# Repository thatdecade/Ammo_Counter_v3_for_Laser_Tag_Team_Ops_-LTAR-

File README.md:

# Ammo Counter for Laser Tag Team Ops (ZZLT)
This is my third attempt at making an Ammo Counter for the LTAR tagger.  This version connects to the LTAR's headphone jack to receive game data.  It was designed in collaboration with Ryan Bales.

The advantages of the ZZLT LTAR Display over my v2 LTAR Number Display are numerous.
- Bar graph indicator to match previous generation LTX displays
- Leverages the LTAR headphone jack to be compatible with all game modes!!!
- Lower power requirements
- Designed to match contours of LTAR iron sight
- Advanced modes to find player number in hosted games
- Easier installation, just 4 wires.

PCB Order Page:             
https://www.oshpark.com/shared_projects/LcxApEpA

Photo Gallery:          
https://www.flickr.com/photos/dwest2/albums/72157642762403194

Install Video:           
https://www.youtube.com/watch?v=OvuctqtzjE8

**Usage:**

The display will turn itself on and off. When you turn the tagger on, the display detects that and turns on. When the display first turns on, it will blink a single LED, just to let you know it's working. When you turn the tagger off, the display will stay on for about 15 seconds, and then turn off.

While you set up the LTAR, be it joining a game, or changing the health/team settings for a grab-and-go game, that single LED will continue to blink.

When the tagger starts it's countdown, the display will start showing how much time is left in the countdown! If you've used an LTX, the way it's shown should be very familiar to you. A blinking LED counts as 1, and a solid LED is 2.

Once the game starts, the countdown display will disappear and one of the mode LEDs at the bottom will light up. This is "Health" mode. It shows how much health you have left. This is displayed as a rough percentage of how much health you started the game with. A blinking LED is 6.25%, and a solid LED is 12.5%. While it may not be an exact display, it will give you an idea of when you need to start worrying.

If you press the button, the mode LED will change, and you'll be in Ammo mode. This shows you how much ammo is left in your clip. This is, once again, a percentage of how much ammo you started with. It will adapt automatically to any weapon, including but not limited to the pistol and machinegun built into the tagger.

One more press of the button, and you're in Shields mode! This one's a bit different. The tagger's shield can only be used in 10-second bursts, so the display shows a percentage based on whether you have 10 seconds worth of shield remaining. While your shield is on, this will show you how much time you have left in this burst of shields. When you turn off your shields, it will show you how much time is left until the cooldown of the shields finishes. The cooldown is shown as a "climbing" percentage, starting at 0% and going up to 100%. Once the cooldown finishes, it goes back to the display of whether you have 10 seconds remaining or not.

There is also a context-sensitive display, that will only be shown in certain types of hosted games. While not all of the features of this mode can be active at the same time, nothing in this mode overlaps between game modes.
- If you're neutralized, the center two LEDs in the vertical bar will be blinking.
- If you're in a zone game, you're neutralized, and the zone is hostile currently, the top and bottom LED of the vertical LED bar will be blinking.
- Some taggers might be able to show when you gain a zone point, in which case the 2nd, 3rd, 6th and 7th LEDs of the vertical LED bar will be lit up.
- If you're in a hunter/hunted game, when the hunting/hunted teams switch, the mode LEDs will show you which team you should be hunting by blinking the mode LED related to that team, and the team you should be avoiding is solid. The Health LED is Team 1, the Ammo LED is Team 2, and the Shield LED is Team 3.

When a game ends, whether by you being tagged out, or the time running out, it will go to a "game over" mode that has a few submodes. All of these modes display information in roughly the same way. Like other numerical modes, a blinking LED is "1", and a solid LED is "2". The top three LEDs of the vertical LED bar show the tens place, and the bottom five show the ones place.
- By default, the "game over" mode shows your player ID. The tens place represents the team, and the ones place represents your player number on that team.
- Some taggers might be able to show your team and player rank, if in a hosted game. If available, you will be able to press the button and cycle through them. After the player ID, first comes your team rank, followed by your personal rank.

This covers the basic operation of the LTAR display! There are a few extra modes, however.
- If you hold the button for a few seconds, all the LEDs will turn on, and the mode will reset to the Health mode. You're now in advanced mode! You can switch back to basic mode the same way.

If you cycle through the modes again, you'll find a few extras, which light up multiple mode LEDs.
- The first Advanced mode, with the Health and Ammo LEDs lit up, is "Game time" mode. In a non-hosted game, this will count up, and show how long you've been playing! This is limited to 69 minutes, however. Past that, it won't show the tens place. In a hosted game, this will count /down/, and tell how many minutes are left in the game.
- The second Advanced mode, with the Ammo and Shield LEDs lit up, shows you who you were last tagged by. This is read the same way as your player ID in game over mode.
- The third Advanced mode, with all three mode LEDs lit up, is your player ID, and is the read the same way as your player ID in game over mode.

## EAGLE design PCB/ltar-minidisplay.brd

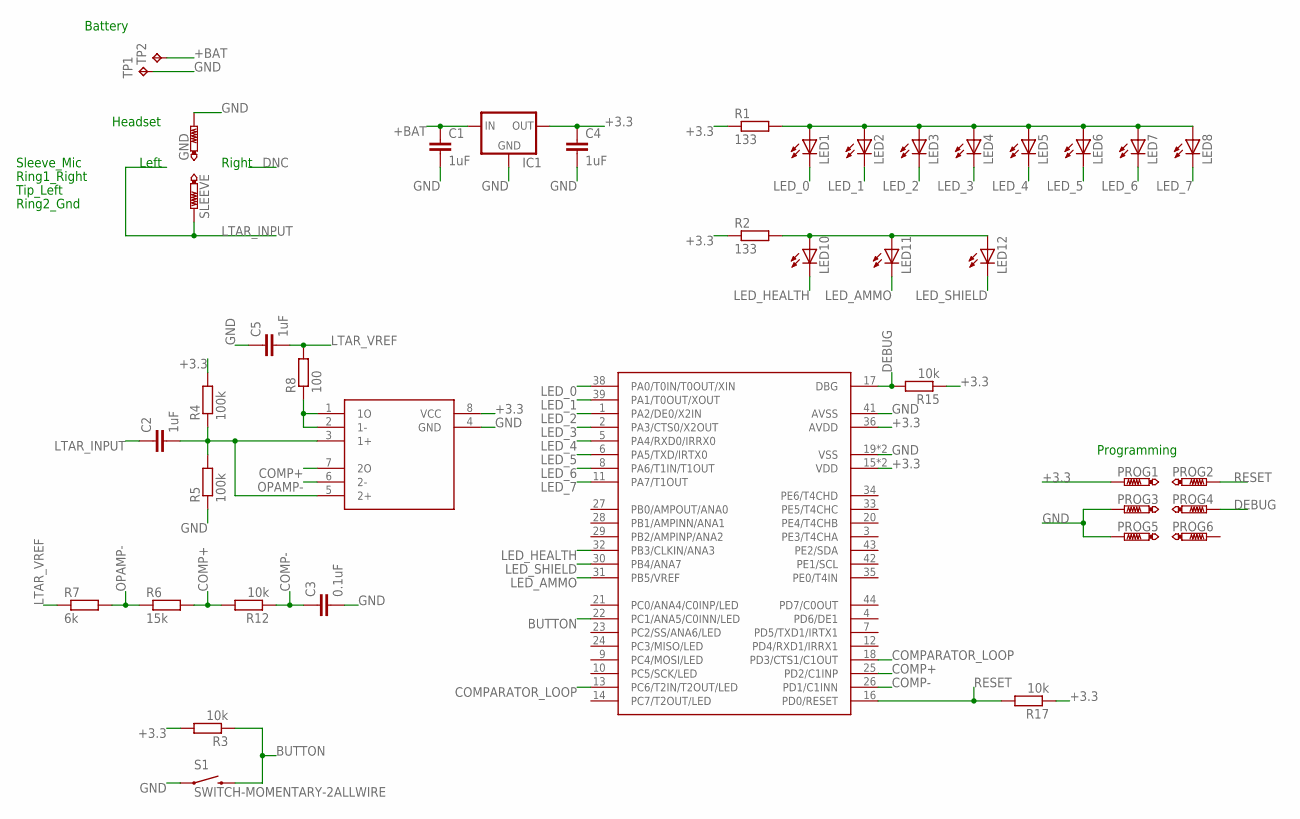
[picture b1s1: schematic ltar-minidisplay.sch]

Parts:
C1, C2, C4, C5: 1uF; C0603
C3: 0.1uF; C0603
GND: PTR1TP11SQ; TP11SQ
IC1: XC63FPM; SOT23
LED1, LED2, LED3, LED4, LED5, LED6, LED7, LED8, LED10, LED11, LED12: LEDCHIPLED_0805; CHIPLED_0805
PROG1, PROG2, PROG3, PROG4, PROG5, PROG6: PTR1TP15SQ; TP15SQ
R1, R2: 133; M0805
R3, R12, R15, R17: 10k; M0805
R4, R5: 100k; M0805
R6: 15k; M0805
R7: 6k; M0805
R8: 100; M0805
S1: SWITCH-MOMENTARY-2ALLWIRE; TACTILE_SWITCH_SMD
SLEEVE: PTR1TP11SQ; TP11SQ
TP1, TP2: TPB1,27; B1,27
U$1: Z8F2480-44; QFP44
U$2: TI_LM258; SO08

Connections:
+3.3: C4.1, IC1.2 (OUT), PROG1.TP, R1.1, R2.1, R3.2, R4.2, R15.1, R17.1, U$1.15 (VDD), U$1.36 (AVDD), U$1.37 (VDD), U$2.8 (VCC)
+BAT: C1.1, IC1.3 (IN), TP2.TP
BUTTON: R3.1, S1.3 (2), S1.4 (2), U$1.22 (PC1/ANA5/C0INN/LED)
COMP+: R6.2, R12.2, U$1.25 (PD2/C1INP), U$2.7 (2O)
COMP-: C3.1, R12.1, U$1.26 (PD1/C1INN)
COMPARATOR_LOOP: U$1.13 (PC6/T2IN/T2OUT/LED), U$1.18 (PD3/CTS1/C1OUT)
DEBUG: PROG4.TP, R15.2, U$1.17 (DBG)
GND: C1.2, C3.2, C4.2, C5.1, GND.TP, IC1.1 (GND), PROG3.TP, PROG5.TP, R5.1, S1.1, S1.2 (1), TP1.TP, U$1.19 (VSS), U$1.40 (VSS), U$1.41 (AVSS), U$2.4 (GND)
LED_0: LED1.C, U$1.38 (PA0/T0IN/T0OUT/XIN)
LED_1: LED2.C, U$1.39 (PA1/T0OUT/XOUT)
LED_2: LED3.C, U$1.1 (PA2/DE0/X2IN)
LED_3: LED4.C, U$1.2 (PA3/CTS0/X2OUT)
LED_4: LED5.C, U$1.5 (PA4/RXD0/IRRX0)
LED_5: LED6.C, U$1.6 (PA5/TXD/IRTX0)
LED_6: LED7.C, U$1.8 (PA6/T1IN/T1OUT)
LED_7: LED8.C, U$1.11 (PA7/T1OUT)
LED_AMMO: LED11.C, U$1.31 (PB5/VREF)
LED_HEALTH: LED10.C, U$1.32 (PB3/CLKIN/ANA3)
LED_SHIELD: LED12.C, U$1.30 (PB4/ANA7)
LTAR_INPUT: C2.1, SLEEVE.TP
LTAR_VREF: C5.2, R7.1, R8.2
unnamed: R8.1, U$2.1 (1O), U$2.2 (1-)
unnamed: LED1.A, LED2.A, LED3.A, LED4.A, LED5.A, LED6.A, LED7.A, LED8.A, R1.2
unnamed: LED10.A, LED11.A, LED12.A, R2.2
OPAMP+: C2.2, R4.1, R5.2, U$2.3 (1+), U$2.5 (2+)
OPAMP-: R6.1, R7.2, U$2.6 (2-)
RESET: PROG2.TP, R17.2, U$1.16 (PD0/RESET)

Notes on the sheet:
Battery
Programming
Headset
Tip_Left
Ring1_Right
Sleeve_Mic
Ring2_Gnd
Right
Left

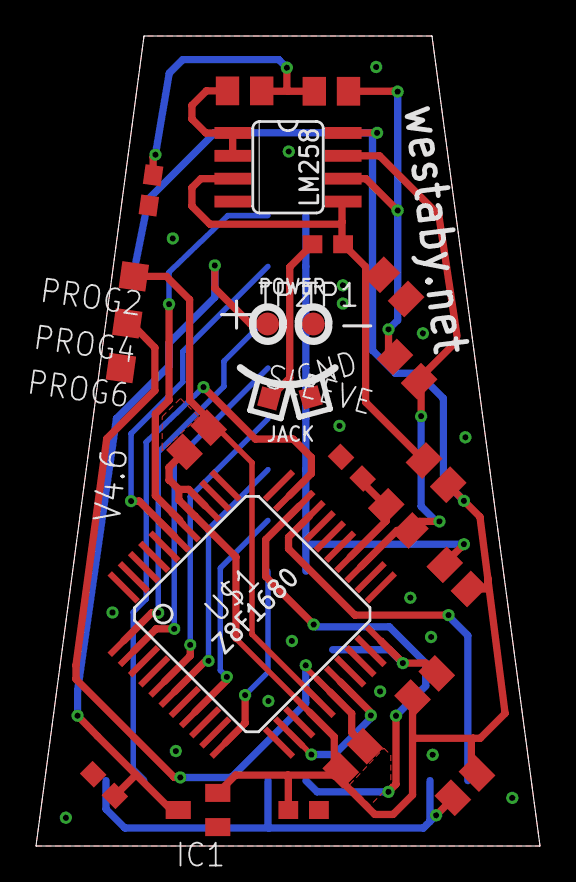
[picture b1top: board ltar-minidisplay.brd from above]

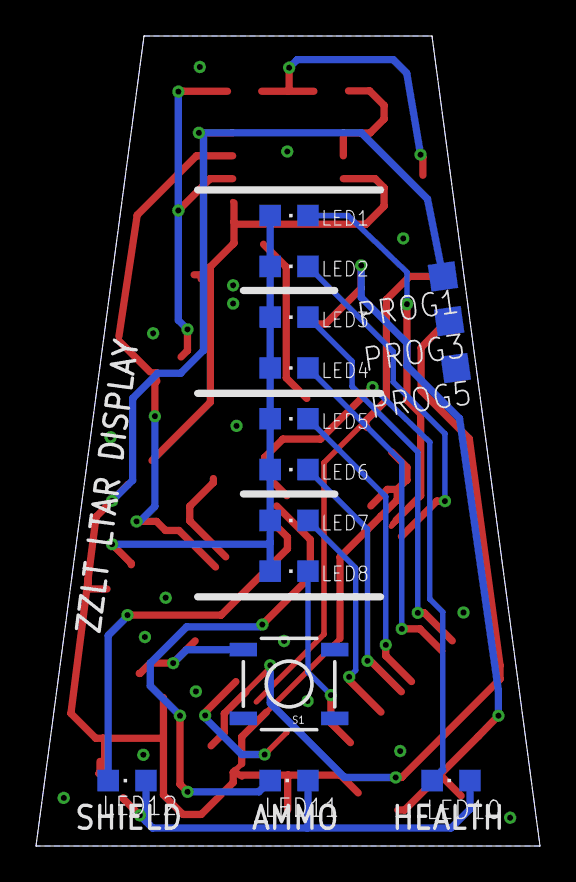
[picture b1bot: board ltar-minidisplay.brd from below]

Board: 2 copper layers, 28.0 x 45.0 mm, 41 parts (15 on the bottom side), 27 nets.

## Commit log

2017-03-23 Rename PCB/ltar-minidisplay.dxf to Hardware/ltar-minidisplay.dxf
